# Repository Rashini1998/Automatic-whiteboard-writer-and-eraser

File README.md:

# Automatic-whiteboard-writer-and-eraser
This project is based on designing a fully automated device that can be used to draw circuits, biological systems by providing the relevant Gcode stored in a micro SD card to it with low cost and higher accuracy and making a fully automated device that can be used to clean large whiteboards by providing a command.

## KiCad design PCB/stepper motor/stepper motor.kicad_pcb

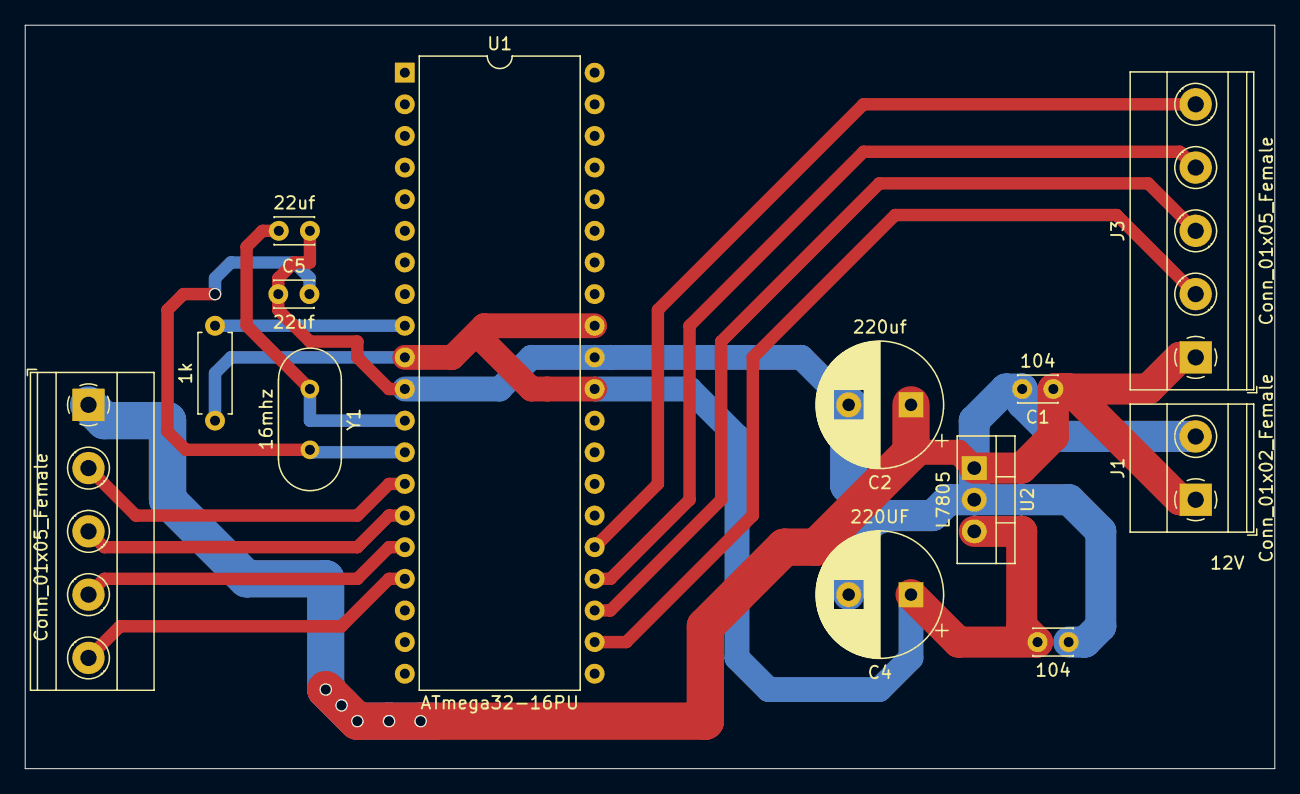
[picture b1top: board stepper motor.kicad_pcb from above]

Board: 2 copper layers, 100.3 x 59.7 mm, 13 parts (0 on the bottom side), 14 nets.

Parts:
C1, C3: 104; C_Disc_D3.0mm_W2.0mm_P2.50mm
C2: 220uf; CP_Radial_D10.0mm_P5.00mm
C4: 220UF; CP_Radial_D10.0mm_P5.00mm
C5, C6: 22uf; C_Disc_D3.0mm_W2.0mm_P2.50mm
J1: Conn_01x02_Female; TerminalBlock_Phoenix_MKDS-1,5-2-5.08_1x02_P5.08mm_Horizont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
J2, J3: Conn_01x05_Female; TerminalBlock_Phoenix_MKDS-1,5-5-5.08_1x05_P5.08mm_Horizont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
R1: 1k; R_Axial_DIN0207_L6.3mm_D2.5mm_P7.62mm_Horizontal
U1: ATmega32-16PU; DIP-40_W15.24mm
U2: L7805; TO-220-3_Vertical
Y1: 16mhz; Crystal_HC49-4H_Vertical

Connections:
5v: C3.1, C4.1, R1.2, U1.10, U1.30, U1.32, U2.3
12v: C1.1, C2.1, J1.1, J2.1, J3.1, U2.1
Externel_clk_1: C5.2, U1.13, Y1.2
Externel_clk_2: C6.2, U1.12, Y1.1
GND: C1.2, C2.2, C3.2, C4.m2, C5.1, C6.1, J1.2, U1.11, U1.31, U2.2
unnamed: R1.1, U1.9
PB0: J2.2, U1.14
PB1: J2.3, U1.15
PB2: J2.4, U1.16
PB3: J2.5, U1.17
PC0: J3.2, U1.22
PC1: J3.3, U1.23
PC2: J3.4, U1.24
PC3: J3.5, U1.25

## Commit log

2022-06-05 Create index
